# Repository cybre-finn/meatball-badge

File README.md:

# Meatball Badge

Wear the NASA meatball logo as a PCB lanyard badge.

Features:
- illuminated vector and stars (reverse mounted LEDs)
- programmable via Arduino IDE
- ESP32 MCU
- USB Type C interface
- Li-ion battery

For (interactive) BOM see the [Instructions page](https://cybre-finn.github.io/meatball-badge/) (german).

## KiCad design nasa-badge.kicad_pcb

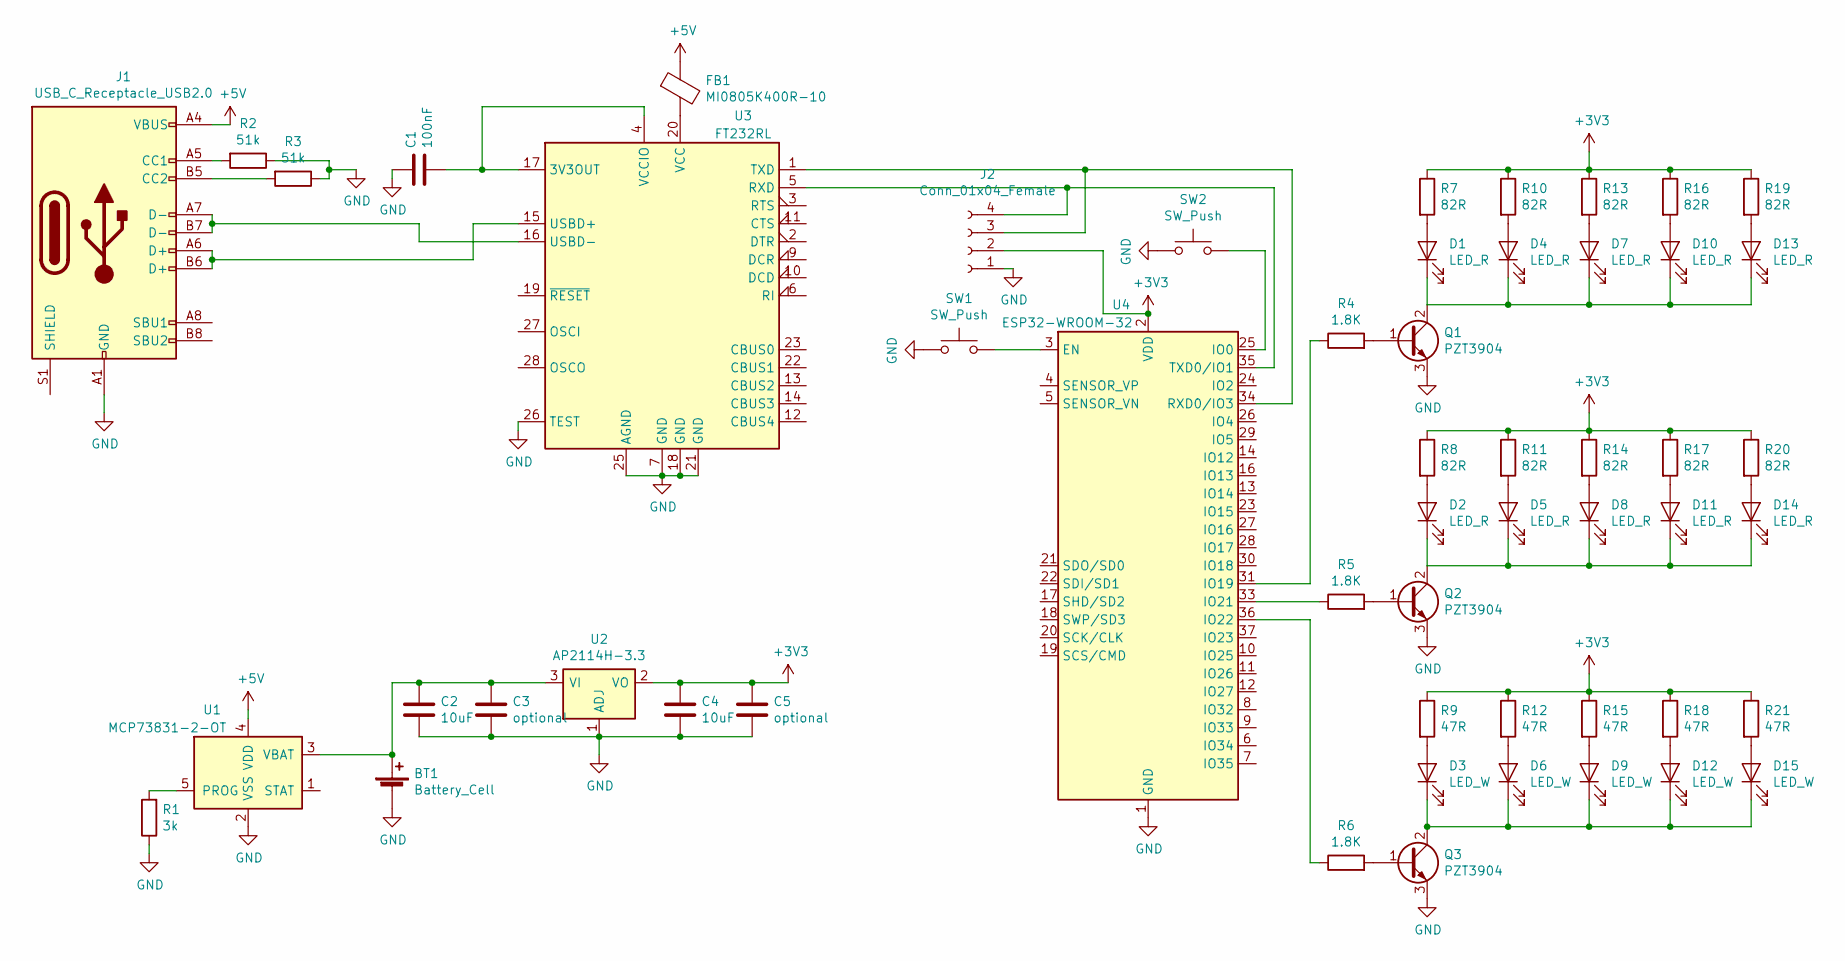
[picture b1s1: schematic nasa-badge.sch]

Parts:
BT1: Battery_Cell; JST_XH_B3B-XH-A_1x03_P2.50mm_Vertical
C1: 100nF; C_0805_2012Metric_Pad1.15x1.40mm_HandSolder
C2, C4: 10uF; C_0805_2012Metric_Pad1.15x1.40mm_HandSolder
C3, C5: optional; C_0805_2012Metric_Pad1.15x1.40mm_HandSolder
D1, D2, D4, D5, D7, D8, D10, D11, D13, D14: LED_R; LED_0603_1608Metric_Pad1.05x0.95mm_HandSolder
D3, D6, D9, D12, D15: LED_W; LED_0603_1608Metric_Pad1.05x0.95mm_HandSolder
FB1: MI0805K400R-10; L_0805_2012Metric_Pad1.15x1.40mm_HandSolder
J1: USB_C_Receptacle_USB2.0; USB_C_Receptacle_HRO_TYPE-C-31-M-12
J2: Conn_01x04_Female; PinSocket_1x04_P2.54mm_Vertical
Q1, Q2, Q3: PZT3904; SOT-223
R1: 3k; R_0805_2012Metric_Pad1.15x1.40mm_HandSolder
R2, R3: 51k; R_0805_2012Metric_Pad1.15x1.40mm_HandSolder
R4, R5, R6: 1.8K; R_0805_2012Metric_Pad1.15x1.40mm_HandSolder
R7, R8, R10, R11, R13, R14, R16, R17, R19, R20: 82R; R_0805_2012Metric_Pad1.15x1.40mm_HandSolder
R9, R12, R15, R18, R21: 47R; R_0805_2012Metric_Pad1.15x1.40mm_HandSolder
SW1, SW2: SW_Push; SW_SPST_FSMSM
U1: MCP73831-2-OT; SOT-23-5
U2: AP2114H-3.3; SOT-223-3_TabPin2
U3: FT232RL; SSOP-28_5.3x10.2mm_P0.65mm
U4: ESP32-WROOM-32

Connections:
+3V3: C4.1, C5.1, J2.2, R7.1, R8.1, R9.1, R10.1, R11.1, R12.1, R13.1, R14.1, R15.1, R16.1, R17.1, R18.1, R19.1, R20.1, R21.1, U2.2 (VO), U4.2 (VDD)
+5V: FB1.1, J1.A4 (VBUS), J1.A9 (VBUS), J1.B4 (VBUS), J1.B9 (VBUS), U1.4 (VDD)
GND: BT1.2 (-), C1.1, C2.2, C3.2, C4.2, C5.2, J1.A1 (GND), J1.A12 (GND), J1.B1 (GND), J1.B12 (GND), J2.1, Q1.3 (E), Q2.3 (E), Q3.3 (E), R1.1, R2.1, R3.1, SW1.1, SW2.1, U1.2 (VSS), U2.1 (ADJ), U3.7 (GND), U3.18 (GND), U3.21 (GND), U3.25 (AGND), U3.26 (TEST), U4.1 (GND), U4.15 (GND), U4.38 (GND), U4.39 (GND)
unnamed: BT1.1 (+), C2.1, C3.1, U1.3 (VBAT), U2.3 (VI)
unnamed: C1.2, U3.4 (VCCIO), U3.17 (3V3OUT)
unnamed: D1.1 (K), D4.1 (K), D7.1 (K), D10.1 (K), D13.1 (K), Q1.2 (C), Q1.4 (C)
unnamed: D1.2 (A), R7.2
unnamed: D2.2 (A), R8.2
unnamed: D3.2 (A), R9.2
unnamed: D4.2 (A), R10.2
unnamed: D5.2 (A), R11.2
unnamed: D6.2 (A), R12.2
unnamed: D7.2 (A), R13.2
unnamed: D8.2 (A), R14.2
unnamed: D9.2 (A), R15.2
unnamed: D10.2 (A), R16.2
unnamed: D2.1 (K), D5.1 (K), D8.1 (K), D11.1 (K), D14.1 (K), Q2.2 (C), Q2.4 (C)
unnamed: D11.2 (A), R17.2
unnamed: D3.1 (K), D6.1 (K), D9.1 (K), D12.1 (K), D15.1 (K), Q3.2 (C), Q3.4 (C)
unnamed: D12.2 (A), R18.2
unnamed: D13.2 (A), R19.2
unnamed: D14.2 (A), R20.2
unnamed: D15.2 (A), R21.2
unnamed: FB1.2, U3.20 (VCC)
unnamed: J1.A5 (CC1), R2.2
unnamed: J1.A6 (D+), J1.B6 (D+), U3.15 (USBD+)
unnamed: J1.A7 (D-), J1.B7 (D-), U3.16 (USBD-)
unnamed: J1.B5 (CC2), R3.2
unnamed: J2.3, U3.1 (TXD), U4.34 (RXD0/IO3)
unnamed: J2.4, U3.5 (RXD), U4.35 (TXD0/IO1)
unnamed: Q1.1 (B), R4.2
unnamed: Q2.1 (B), R5.2
unnamed: Q3.1 (B), R6.2
unnamed: R1.2, U1.5 (PROG)
unnamed: R4.1, U4.31 (IO19)
unnamed: R5.1, U4.33 (IO21)
unnamed: R6.1, U4.36 (IO22)
unnamed: SW1.2, U4.3 (EN)
unnamed: SW2.2, U4.25 (IO0)

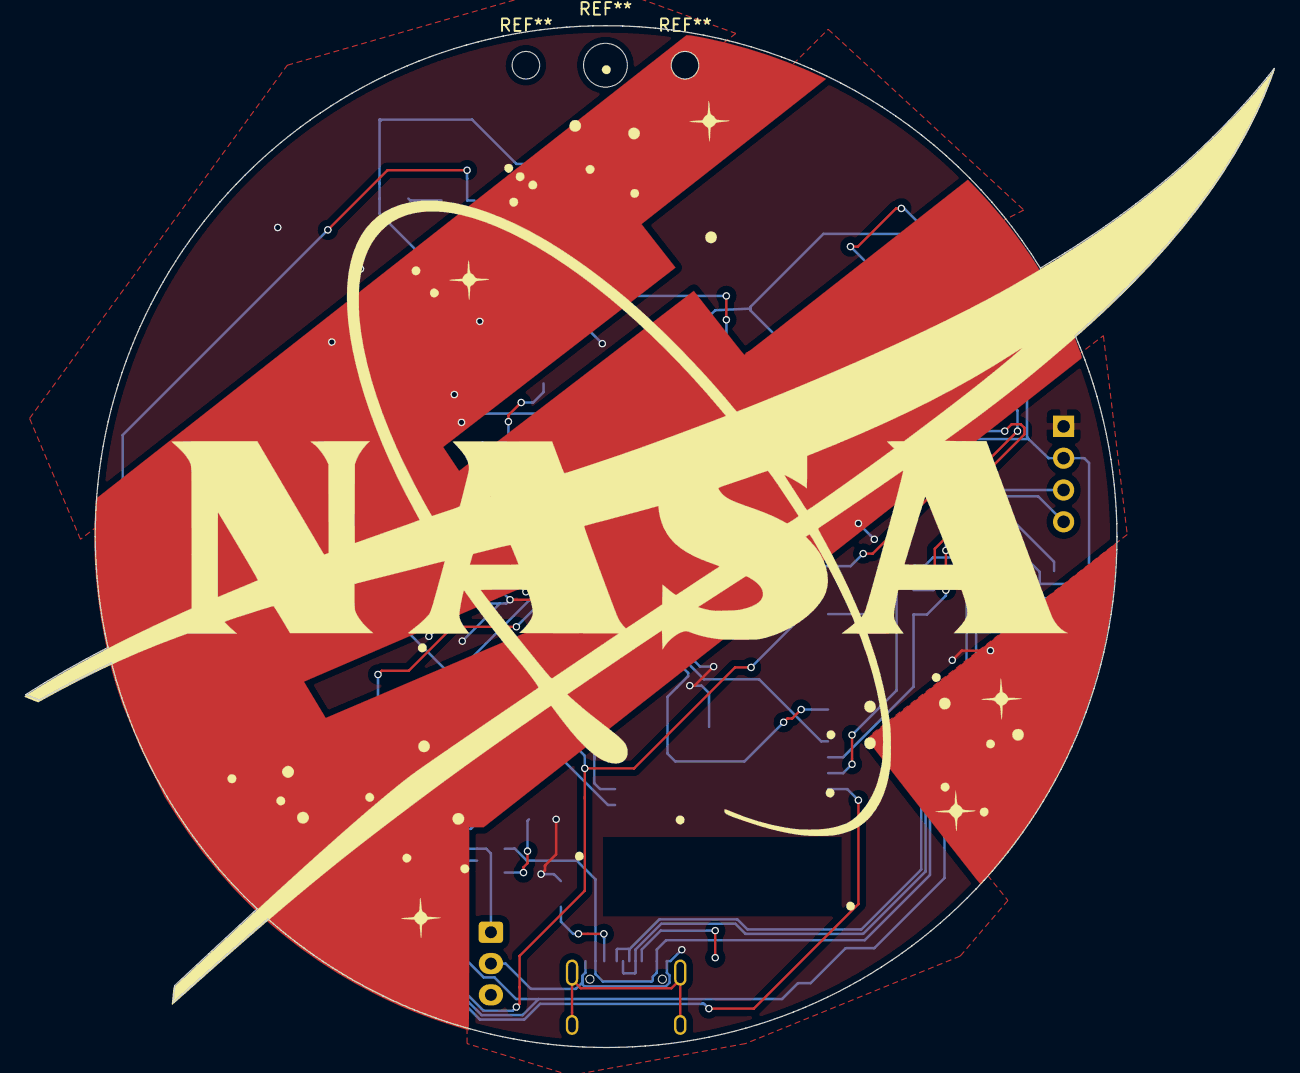
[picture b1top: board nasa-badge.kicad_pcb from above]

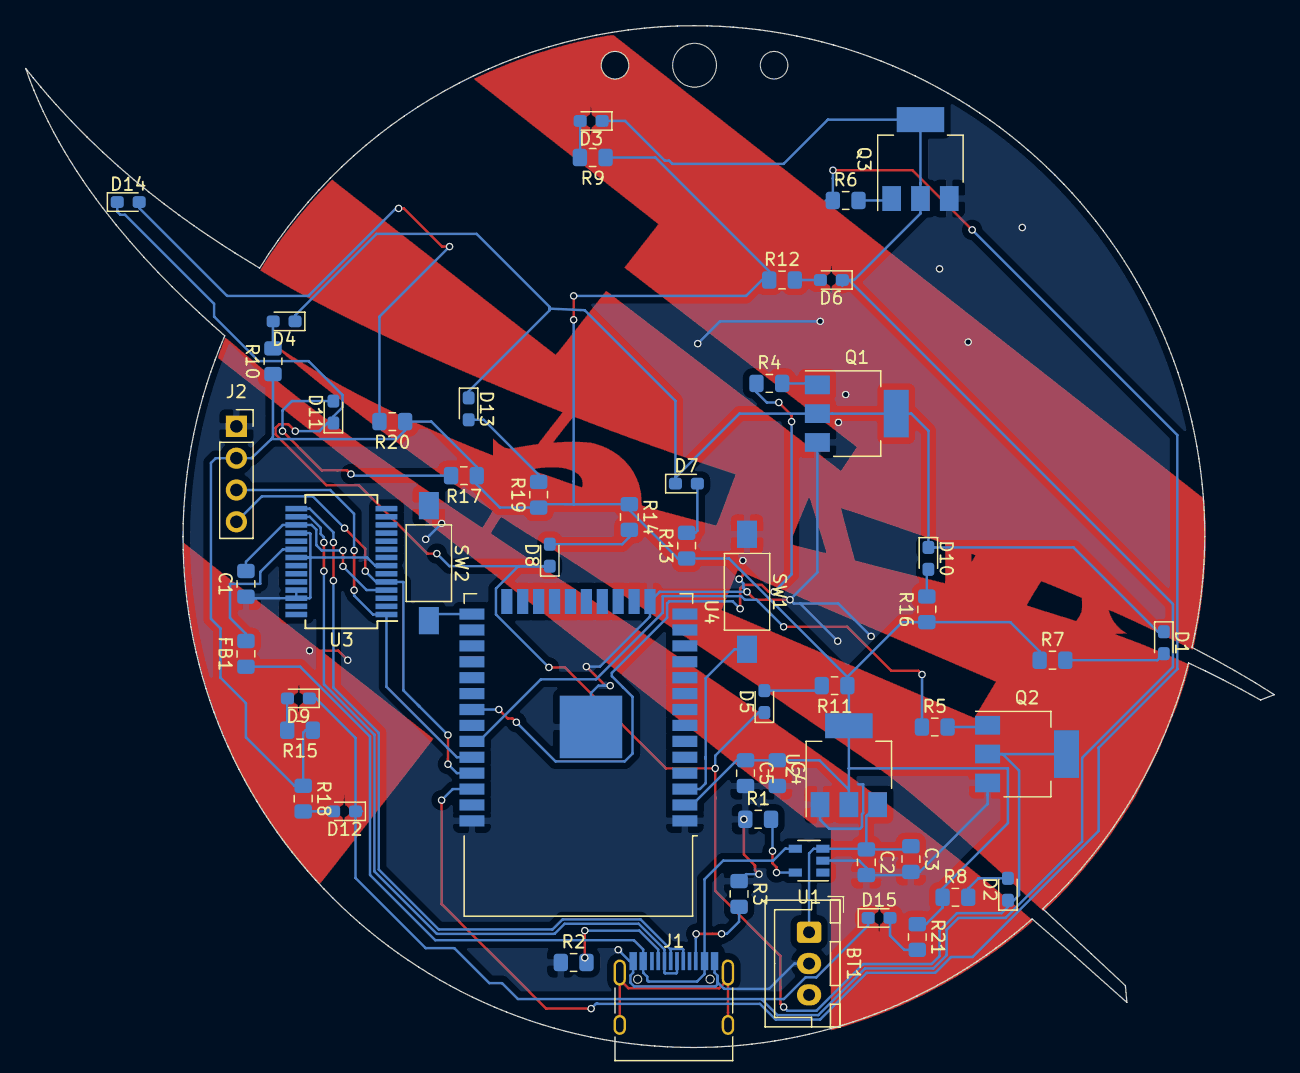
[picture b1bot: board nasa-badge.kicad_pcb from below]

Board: 2 copper layers, 99.7 x 81.6 mm, 54 parts (54 on the bottom side), 39 nets.

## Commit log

2020-08-14 rev 0.2
2020-08-14 subdirectory for hardware
2020-08-14 github pages test
2020-08-15 add docs
2020-08-15 add ibom
2020-08-15 add board version number
2020-08-15 make pictures work
2020-08-15 add link to ibom
2020-08-15 fix links
2020-08-15 fix images
2024-01-11 Fix README.md
